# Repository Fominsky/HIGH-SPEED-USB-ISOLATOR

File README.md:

# High-speed USB isolator based on ADuM3165/ADuM3166

When connecting a USB device to a PC or laptop, there is a risk that the device may be faulty or may fail during operation. This is especially relevant during the development and debugging of devices that connects to your PC.

Connecting a malfunctioning USB device can easily lead to the failure of the USB hub in your PC, and in the case of laptops, the hub is often located on the same substrate as the processor. Thus, there is a risk that if something goes wrong, you will have to replace the processor in your laptop.

A USB isolator will protect your PC from USB-related issues. In the worst-case scenario, the ADuM3165/6 chip itself may fail, but your PC should be fine.

## Description
The device has 3 USB ports: Host USB, External Power USB, and Device USB.
Host USB is connected to your computer, Device USB is connected to your device that needs to be isolated, and External Power USB is connected to an external power source for powering the device connected to the Device USB port.

The device has its own low-power galvanically isolated DC-DC converter. The DC-DC converter also has converter overload protection. Therefore, the device can be used without external power for communication with low-power devices or devices that have their own power source.

The maximum current of the DC-DC converter is 200 mA. If this value is exceeded, the load is disconnected, and the "Overload" red LED lights up. The load will be disconnected either until the protection is reset by pressing SW1 button (Reset_Button) or until the USB is disconnected from the host USB and reconnected. 

To connect more powerful loads, you can use the External Power USB port. It is important to note that this USB is not isolated from the Device USB but is not electrically connected to the Host USB. A good solution would be to connect a power adapter from a mobile device to the external power USB.

When external power is connected, the built-in DC-DC converter is disabled. Note: as I mentioned before, the overload protection only works with the built-in DC-DC converter, so the overload protection is also disabled.

##

This Repository contains Gerber files, BOM, and step model. All you need to make an isolator.

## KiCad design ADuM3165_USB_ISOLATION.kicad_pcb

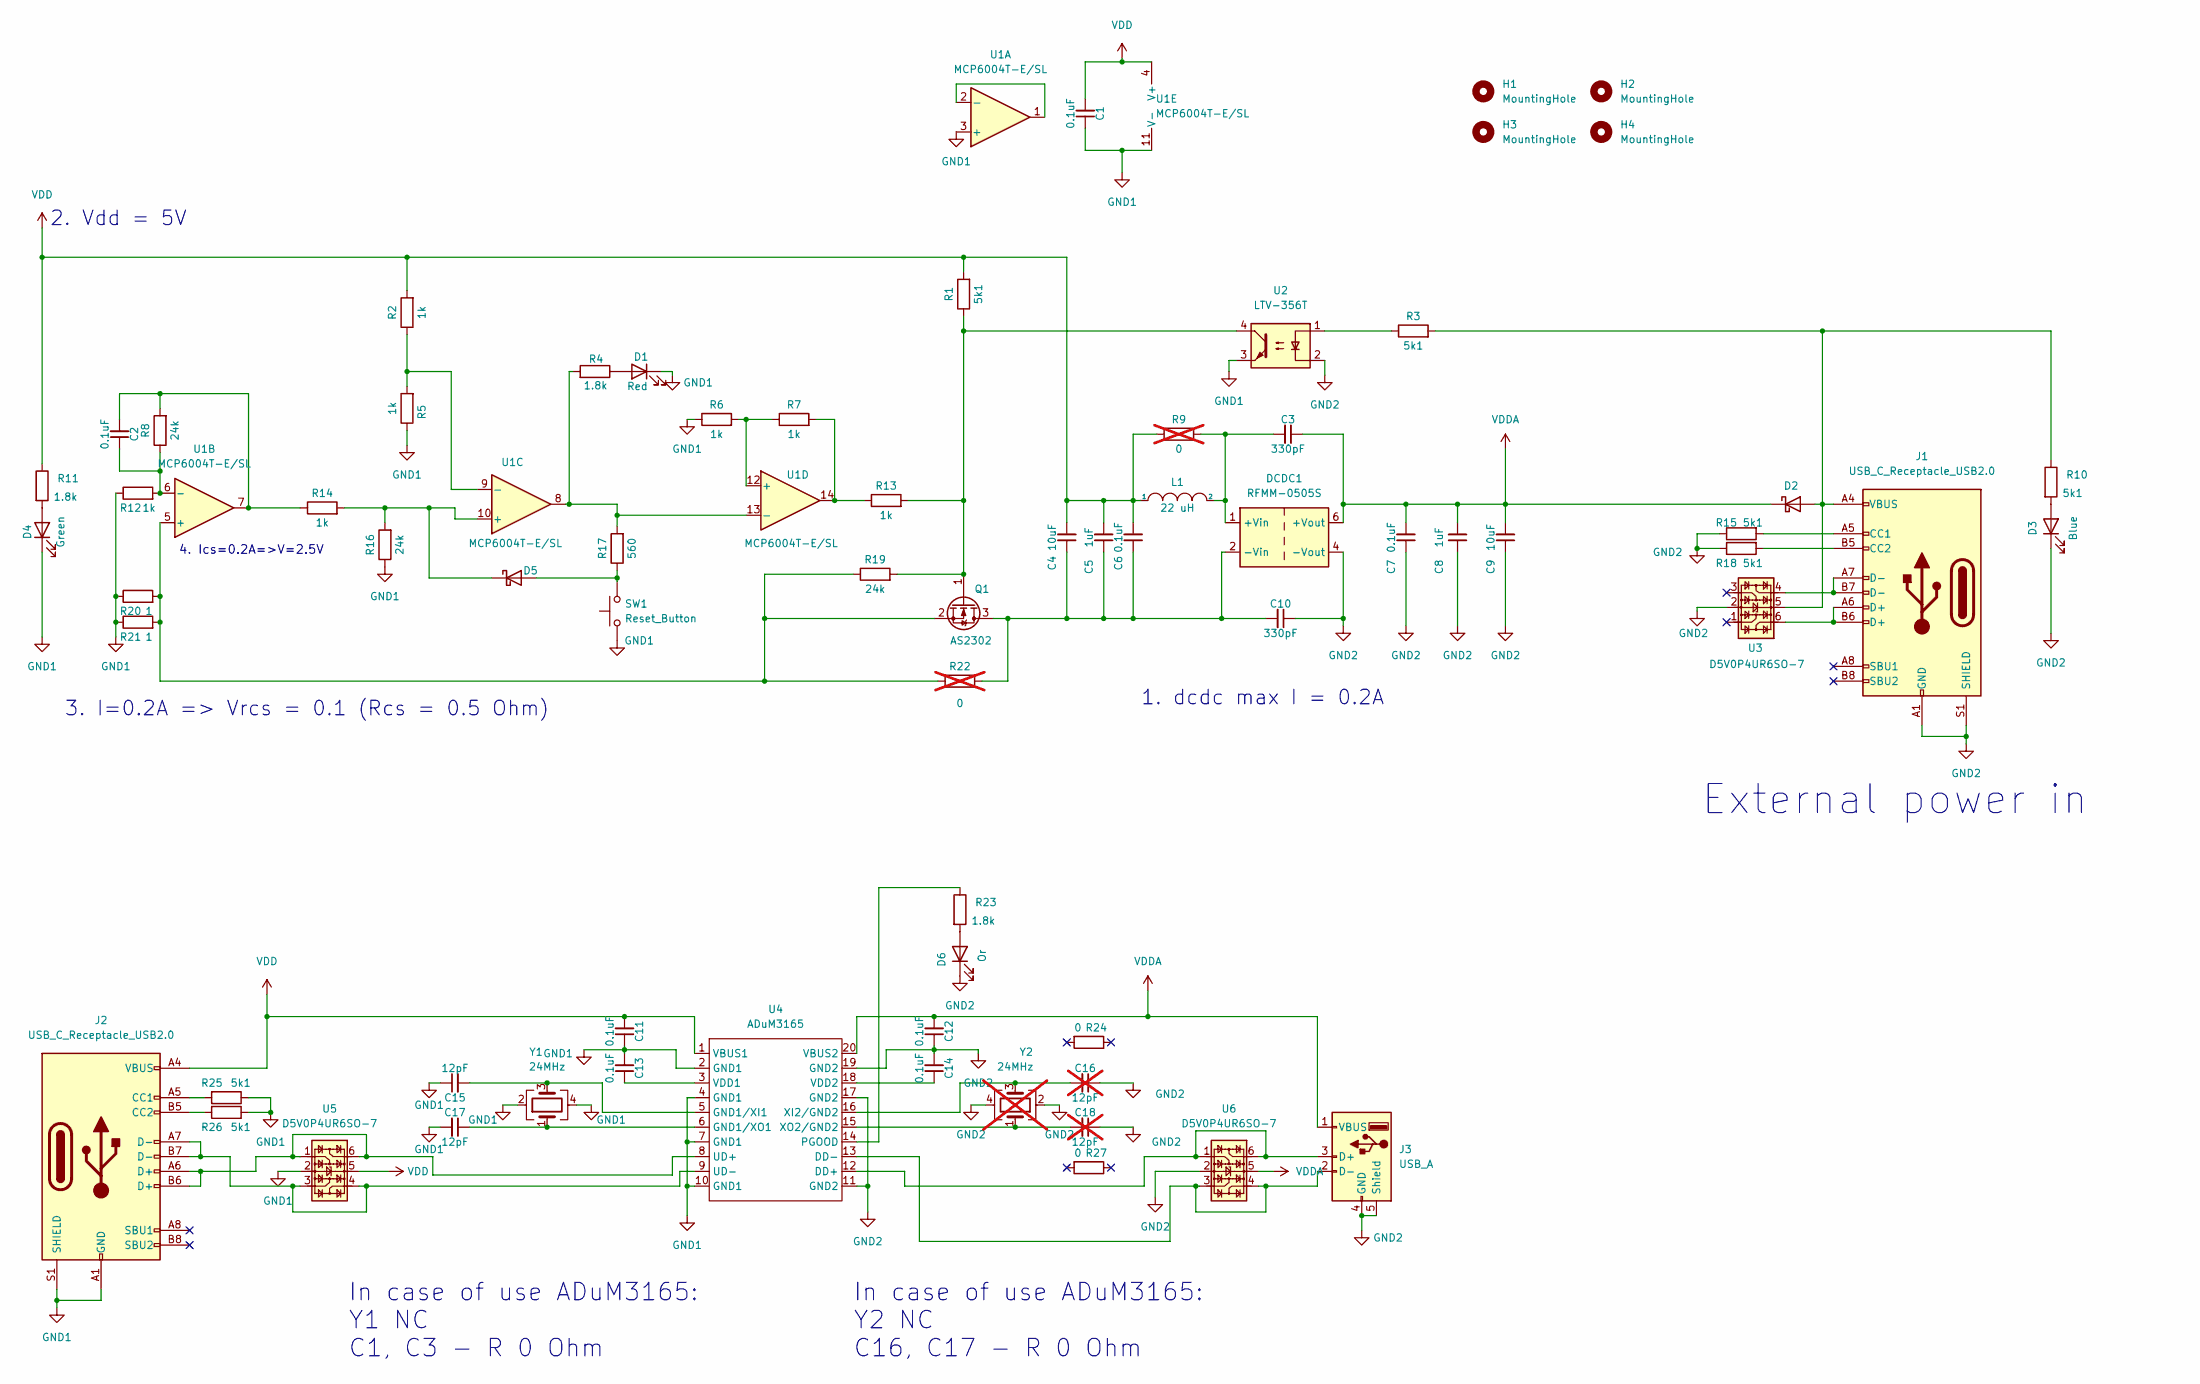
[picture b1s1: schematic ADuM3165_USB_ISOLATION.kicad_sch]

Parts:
C1, C2, C6, C7, C11, C12, C13, C14: 0.1uF; C_0603_1608Metric; Voltage 50
C3, C10: 330pF; C_Rect_L10.0mm_W3.0mm_P7.50mm_MKS4; Voltage 1000
C4, C9: 10uF; C_0805_2012Metric; Voltage 16
C5, C8: 1uF; C_0603_1608Metric; Voltage 50
C15, C17: 12pF; C_0603_1608Metric; Voltage 50
C16, C18: 12pF; C_0603_1608Metric; Voltage 50; not fitted
D1: Red; LED_0603_1608Metric
D2, D5: 10v 3A; D_SOD-323; Voltage 10v
D3: Blue; LED_0603_1608Metric
D4: Green; LED_0603_1608Metric
D6: Or; LED_0603_1608Metric
DCDC1: RFMM-0505S; RFMM_RFB0505S
H1, H2, H3, H4: MountingHole; MountingHole_3.2mm_M3_DIN965
J1, J2: USB_C_Receptacle_USB2.0; USB_C_Receptacle_GCT_USB4105-xx-A_16P_TopMnt_Horizontal
J3: USB_A; USB_A_CONNFLY_DS1095-WNR0
L1: 22 uH; L_Taiyo-Yuden_MD-3030
Q1: AS2302; SOT-23; Voltage 20V 3A
R1, R3, R10, R15, R18, R25, R26: 5k1; R_0603_1608Metric
R2, R5, R6, R7, R12, R13, R14: 1k; R_0603_1608Metric
R4, R11, R23: 1.8k; R_0603_1608Metric
R8, R16, R19: 24k; R_0603_1608Metric
R9, R22: 0; R_0603_1608Metric; not fitted
R17: 560; R_0603_1608Metric
R20, R21: 1; R_0603_1608Metric
R24, R27: 0; R_0603_1608Metric
SW1: Reset_Button; SW_Tactile_SPST_Angled_PTS645Vx58-2LFS
U1: MCP6004T-E/SL; SOIC-14_3.9x8.7mm_P1.27mm
U2: LTV-356T; SO-4_4.4x3.6mm_P2.54mm
U3, U5, U6: D5V0P4UR6SO-7; SOT-23-6
U4: ADuM3165; SSOP-20_5.3x7.2mm_P0.65mm
Y1: 24MHz; Crystal_SMD_2016-4Pin_2.0x1.6mm
Y2: 24MHz; Crystal_SMD_2016-4Pin_2.0x1.6mm; not fitted

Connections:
GND1: C1.1, C11.1, C13.2, C15.1, C17.2, D1.1 (K), D4.1 (K), J2.A1 (GND), J2.A12 (GND), J2.B1 (GND), J2.B12 (GND), J2.S1 (SHIELD), R5.1, R6.1, R12.1, R16.1, R20.1, R21.1, R25.1, R26.1, SW1.1, U1.3 (+), U1.11 (V-), U2.3, U4.2 (GND1), U4.4 (GND1), U4.7 (GND1), U4.10 (GND1), U5.2, Y1.2, Y1.4
GND2: C7.1, C8.1, C9.1, C10.1, C12.1, C14.2, C16.1, C18.1, D3.1 (K), D6.1 (K), DCDC1.4 (-Vout), DCDC1.5 (-Vout), J1.A1 (GND), J1.A12 (GND), J1.B1 (GND), J1.B12 (GND), J1.S1 (SHIELD), J3.4 (GND), J3.5 (Shield), R15.1, R18.1, U2.2, U3.2, U4.11 (GND2), U4.17 (GND2), U4.19 (GND2), U6.2, Y2.2, Y2.4
unnamed: C2.2, R8.2, R14.1, U1.7
unnamed: D1.2 (A), R4.1
unnamed: D2.2 (A), J1.A4 (VBUS), J1.A9 (VBUS), J1.B4 (VBUS), J1.B9 (VBUS), R3.2, R10.1, U3.5
unnamed: D3.2 (A), R10.2
unnamed: D4.2 (A), R11.2
unnamed: D5.2 (A), R17.1, SW1.2
unnamed: D5.1 (K), R14.2, R16.2, U1.10 (+)
unnamed: D6.2 (A), R23.2
unnamed: C3.2, DCDC1.1 (+Vin), L1.2, R9.2
unnamed: C4.1, C5.1, C6.1, C10.2, DCDC1.2 (-Vin), Q1.3 (D), R22.2
unnamed: J1.A5 (CC1), R15.2
unnamed: J1.B5 (CC2), R18.2
unnamed: J1.A6 (D+), J1.B6 (D+), U3.6
unnamed: J1.A7 (D-), J1.B7 (D-), U3.4
unnamed: J2.A5 (CC1), R25.2
unnamed: J2.B5 (CC2), R26.2
unnamed: J3.3 (D+), U4.12 (DD+), U6.1, U6.6
unnamed: J3.2 (D-), U4.13 (DD-), U6.3, U6.4
unnamed: Q1.1 (G), R1.1, R13.2, R19.2, U2.4
unnamed: Q1.2 (S), R19.1, R20.2, R21.2, R22.1, U1.5 (+)
unnamed: R3.1, U2.1
unnamed: R7.2, R13.1, U1.14
unnamed: U1.1, U1.2 (-)
unnamed: C2.1, R8.1, R12.2, U1.6 (-)
unnamed: R2.1, R5.2, U1.9 (-)
unnamed: R6.2, R7.1, U1.12 (+)
unnamed: R4.2, R17.2, U1.8, U1.13 (-)
unnamed: C15.2, U4.5 (GND1/XI1), Y1.3
unnamed: C17.1, U4.6 (GND1/XO1), Y1.1
unnamed: R23.1, U4.14 (PGOOD)
unnamed: J2.A6 (D+), J2.B6 (D+), U4.8 (UD+), U5.1, U5.6
unnamed: J2.A7 (D-), J2.B7 (D-), U4.9 (UD-), U5.3, U5.4
unnamed: C13.1, U4.3 (VDD1)
unnamed: C14.1, U4.18 (VDD2)
unnamed: C16.2, U4.16 (XI2/GND2), Y2.3
unnamed: C18.2, U4.15 (XO2/GND2), Y2.1
VDD: C1.2, C4.2, C5.2, C6.2, C11.2, J2.A4 (VBUS), J2.A9 (VBUS), J2.B4 (VBUS), J2.B9 (VBUS), L1.1, R1.2, R2.2, R9.1, R11.1, U1.4 (V+), U4.1 (VBUS1), U5.5
VDDA: C3.1, C7.2, C8.2, C9.2, C12.2, D2.1 (K), DCDC1.6 (+Vout), DCDC1.7 (+Vout), J3.1 (VBUS), U4.20 (VBUS2), U6.5

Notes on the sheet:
3. I=0.2A => Vrcs = 0.1 (Rcs = 0.5 Ohm)
4. Ics=0.2A=>V=2.5V
In case of use ADuM3165: Y1 NC C1, C3 - R 0 Ohm
In case of use ADuM3165: Y2 NC C16, C17 - R 0 Ohm
1. dcdc max I = 0.2A
External power in
2. Vdd = 5V

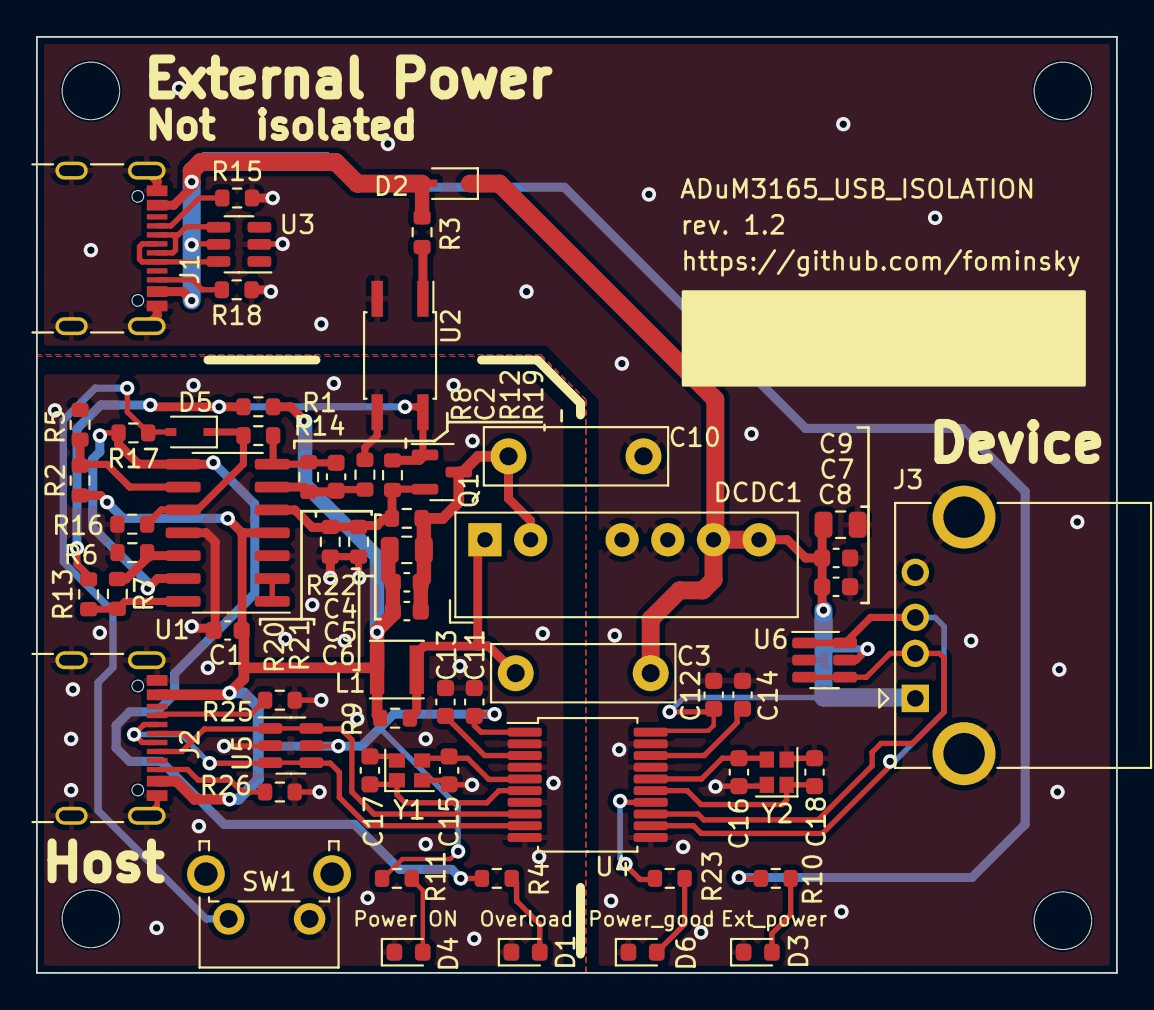
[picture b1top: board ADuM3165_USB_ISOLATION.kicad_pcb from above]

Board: 2 copper layers, 60.0 x 52.0 mm, 68 parts (0 on the bottom side), 40 nets.

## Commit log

2023-12-12 init comit
2023-12-13 bom fix, gitignores added
2024-03-25 backups is added to gitignore
2024-03-25 schematic is updated to actual version
2024-03-25 Overload protection simulation is added
2024-03-27 change note on schematic
